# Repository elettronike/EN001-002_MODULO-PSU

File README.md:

# EN001-002_MODULO-PSU

"MODULO" series PSU board

## Design

Design considerations and references are reported in the [design file](./Design/design.md)

### EDA - Kicad specific

The project is developed using Kicad-8.4.

The component library is managed using the new

## Realease

Kikad production files are generated using the kicad [CLI interface](https://docs.kicad.org/8.0/en/cli/cli.html#introduction_to_the_kicad_command_line_interface).

the command `make` will generate the production file in the folder *release*:

| ID | Document                   | Format |
| :-: | :------------------------- | :----- |
| 1 | BOM with JLCPCB template   | CSV    |
| 2 | Gerber files               | IPCxxx |
| 3 | Drill Files                | .drl   |
| 4 | Schematic                  | PDF    |
| 5 | Manufacturing Instructions | PDF    |

## TODO

- [ ] 	Fix the variable override: `-D Revision=1.2`
- [X] 	Reference,Value,Case,MNFR-1,MNFR-1-PN,SUPP-1,SUPP-1-CODE,SUPP-1-UNIT-PRICE ,
- [ ] 	testo di prova
	 	lungo
- [ ] 	secondo  esto

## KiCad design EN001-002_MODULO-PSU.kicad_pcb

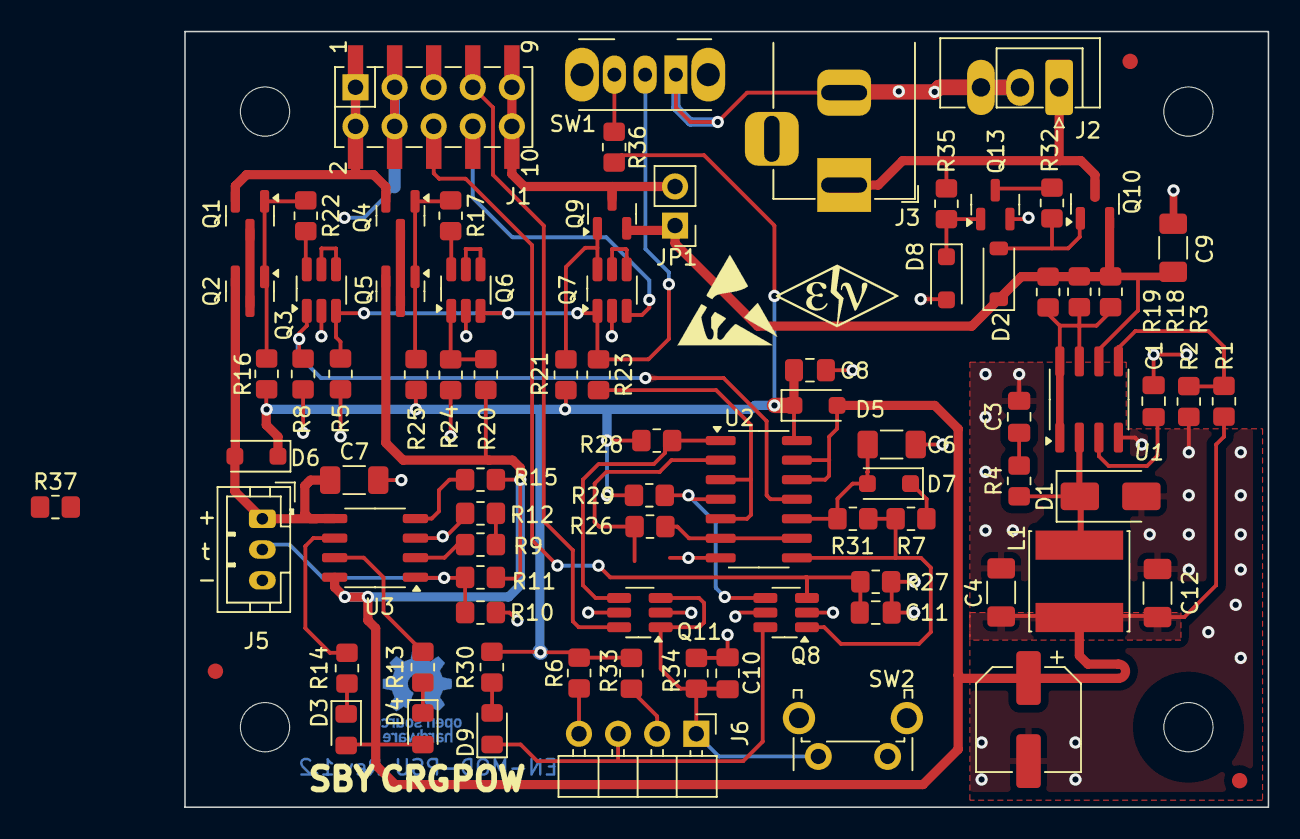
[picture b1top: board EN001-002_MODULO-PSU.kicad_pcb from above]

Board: 2 copper layers, 70.4 x 50.4 mm, 90 parts (1 on the bottom side), 53 nets.

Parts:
C1, C3: 470pF; C_0805_2012Metric_Pad1.18x1.45mm_HandSolder
C2: 470uF; CP_Elec_6.3x7.7
C4, C6, C7, C9, C12: 10uF; C_1206_3216Metric_Pad1.33x1.80mm_HandSolder
C8, C10, C11: 10nF; C_0805_2012Metric_Pad1.18x1.45mm_HandSolder
D1: 550mV@5A; D_SMA
D2: 10V 500mW; D_SOD-123
D3, D4, D9: LED_Filled; LED_0805_2012Metric_Pad1.15x1.40mm_HandSolder
D5, D6, D7, D8: 600mV@200mA; D_SOD-123F
FID1, FID2, FID3: Fiducial; Fiducial_1mm_Mask2mm
H1, H2, H3, H4: MountingHole M3; MountingHole_3.2mm_M3
J1: 2x5P 2.54mm; PinSocket_2x05_P2.54mm_V_THT_SMD
J2: Conn_01x02; PhoenixContact_MC_1,5_2-G-5.08_1x02_P5.08mm_Horizontal
J3: Barrel_Jack_Switch; BarrelJack_Horizontal
J5: 1x3P 2mm; JST_PH_B3B-PH-K_1x03_P2.00mm_Vertical
J6: Conn_01x04; PinHeader_1x04_P2.54mm_Horizontal
JP1: Jumper_2_Bridged; PinHeader_1x02_P2.54mm_Vertical
L1: 100 uH; L_Changjiang_FNR6045S
Q1, Q2, Q4, Q5, Q9, Q10: AO3401; SOT-23
Q3, Q6, Q7, Q8, Q11: KY6802; SOT-23-6_Handsoldering
Q13: MMBT2222A; SOT-23
R1: 3k; R_0805_2012Metric_Pad1.20x1.40mm_HandSolder
R2, R6, R9, R10, R11, R12, R13, R14, R17, R22, R23, R30, R33, R36: 1k; R_0805_2012Metric_Pad1.20x1.40mm_HandSolder
R3, R18, R19: 1R; R_0805_2012Metric_Pad1.20x1.40mm_HandSolder
R4: TBD; R_0805_2012Metric_Pad1.20x1.40mm_HandSolder
R5, R8, R24, R26, R37: 100k; R_0805_2012Metric_Pad1.20x1.40mm_HandSolder
R7, R16, R20, R21, R25, R27, R28, R29, R32, R34, R35: 10k; R_0805_2012Metric_Pad1.20x1.40mm_HandSolder
R15: 0R1; R_0805_2012Metric_Pad1.20x1.40mm_HandSolder
R31: 1M; R_0805_2012Metric_Pad1.20x1.40mm_HandSolder
SW1: SK12D07VG3; SW_Slide_SPDT_Angled_CK_OS102011MA1Q
SW2: TC-6615-7-260G; SW_Tactile_SPST_Angled_PTS645Vx58-2LFS
SYM1: ESD SYMBOL; ESD-Logo_6.6x6mm_SilkScreen
SYM2: IT0000__; OSHW-Logo_5.7x6mm_Copper
U1: AZ34063UMTR-G1; SOIC-8_3.9x4.9mm_P1.27mm
U2: 74HC132D,653; SOIC-14_3.9x8.7mm_P1.27mm
U3: TP4056; SOP-8_3.9x4.9mm_P1.27mm

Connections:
/5V#: Q3.1 (G), R8.1, U2.11
/5Vout: C2.1, C4.1, C12.1, D3.2 (A), D4.2 (A), D5.2 (A), L1.2, Q5.2 (S), R1.1, R11.1, R15.1, R20.1, U2.12, U2.13, U3.8 (CE)
/$BUTTON: J1.7, Q11.6 (D)
/$PDOWN: C11.1, J1.6, Q8.3 (G), R27.1
/DRIVE: Q3.3 (G), Q6.3 (G), Q7.1 (G), R5.1, R23.1, SW1.2 (B), U2.5
/DRIVE#: U2.2, U2.6, U2.9
/LEDC: D9.1 (K), J6.3, Q8.6 (D)
/POWUP: C10.1, J6.1, Q11.1 (G), Q11.3 (G), R34.1, SW2.2 (B)
/RESET: Q8.4 (D), R29.1, U2.4
/SET: Q11.4 (D), R28.1, U2.1
/T_BATT: J5.2, R10.1, R11.2, U3.1 (TEMP)
/VIN: J2.1, J3.1, Q10.3 (D), R35.1
/VINS: C9.1, D2.1 (K), JP1.1 (A), Q9.2 (S), Q10.2 (S), R3.1, R18.1, R19.1, R21.2, U1.6 (VCC)
/VLOGIC: C8.1, D5.1 (K), D6.1 (K), R6.2, R16.2, R25.2, R28.2, R29.2, R30.1, R33.1, R36.2, U2.14 (VCC)
/VOUT: J1.1, J1.2, Q1.2 (S), Q4.2 (S)
/VPOW: J1.9, J1.10, JP1.2 (B), Q9.3 (D)
/VPOW_EN: J1.8, Q7.3 (G)
/V_BATT: C7.1, D6.2 (A), J5.1, Q2.2 (S), U3.5 (BAT)
/comp: R1.2, R2.1, U1.5 (comp)
GND: C1.2, C2.2, C3.2, C4.2, C6.2, C7.2, C8.2, C9.2, C10.2, C11.2, C12.2, D1.2 (A), D8.2 (A), J1.3, J1.4, J2.2, J3.2, J5.3, Q3.2 (S), Q6.2 (S), Q7.2 (S), Q8.2 (S), Q8.5 (S), Q11.2 (S), Q11.5 (S), Q13.2 (E), R2.2, R5.2, R8.2, R10.2, R12.1, R24.2, R26.2, R27.2, R34.2, R37.2, SW1.1 (A), U1.4 (GND), U2.7 (GND), U3.3 (GND)
unnamed: C3.1, R4.2
unnamed: D1.1 (K), L1.1, R4.1, U1.2 (SWE)
unnamed: D2.2 (A), Q10.1 (G), R32.1
unnamed: D3.1 (K), R14.1
unnamed: D4.1 (K), R13.1
unnamed: D7.2 (A), R7.2
unnamed: C6.1, D7.1 (K), R31.2, U2.10
unnamed: D8.1 (K), Q13.1 (B), R35.2
unnamed: D9.2 (A), R30.2
unnamed: J6.2, R33.2, SW2.1 (A)
unnamed: J6.4, R6.1
unnamed: Q1.3 (D), Q2.3 (D), R26.1
unnamed: Q1.1 (G), Q2.1 (G), R16.1, R22.1
unnamed: Q3.6 (D), R22.2
unnamed: Q3.4 (D), Q3.5 (S)
unnamed: Q4.3 (D), Q5.3 (D), R37.1
unnamed: Q4.1 (G), Q5.1 (G), R17.1, R25.1
unnamed: Q6.6 (D), R17.2
unnamed: Q6.1 (G), R20.2, R24.1
unnamed: Q6.4 (D), Q6.5 (S)
unnamed: Q7.6 (D), Q9.1 (G), R21.1
unnamed: Q7.4 (D), Q7.5 (S)
unnamed: Q8.1 (G), R7.1, R31.1, U2.8
unnamed: Q13.3 (C), R32.2
unnamed: R9.1, R12.2
unnamed: R23.2, U2.3
unnamed: R36.1, SW1.3 (C)
unnamed: C1.1, U1.3 (CAP)
unnamed: R3.2, R18.2, R19.2, U1.1 (SWC), U1.7 (sense), U1.8 (DRV)
unnamed: R13.2, U3.7 (CHRG)
unnamed: R9.2, U3.2 (PROG)
unnamed: R14.2, U3.6 (STDBY)
unnamed: R15.2, U3.4 (VCC)

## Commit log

2024-08-19 added initial gitignore
2024-08-19 ignore temporary files
2024-08-19 added project files
2024-08-19 makefile to generate release using CLI
2024-08-23 created todo list
2024-08-23 redefinition of PRJ variable for better use
2024-08-23 created DESIGN FILE to hol design considerations
2024-08-23 design file integration in readme
2024-08-23 readme: release informations
2024-08-25 cli commands for pcb fabrication
2024-08-25 minor changes
2024-08-25 minor on schematic release notes
2024-08-25 jlcpcb assembly file generation
2024-08-25 source files
2024-08-25 exclude zip files
2024-08-25 source files elettronike page layout
2024-08-31 pcb layout
2024-08-31 ignore autosaved files
2024-09-08 kicad 8.0.5
2024-09-14 Rotated D7, SW2 in parallel to external switch, removed R26 replaced with short, removed C5
2024-09-14 R21 moved betwwen source and drain of Q9
2024-09-14 Added R26 and R37 100k pulldown on back-to-back pass mosfet
2024-09-14 schematic minor rearrangments
2024-09-14 Applied schematic mods
2024-09-15 Adde Q12 to drive power-up from microcontroller
